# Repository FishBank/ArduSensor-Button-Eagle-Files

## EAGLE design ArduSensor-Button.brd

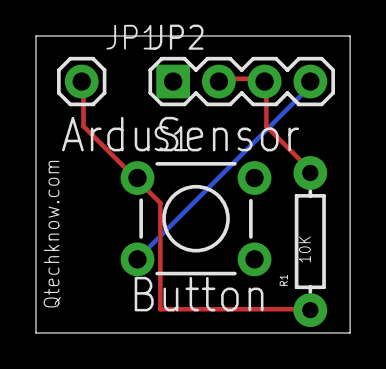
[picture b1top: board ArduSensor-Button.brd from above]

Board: 2 copper layers, 17.4 x 16.5 mm, 4 parts (0 on the bottom side), 3 nets.

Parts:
JP1: M01PTH; 1X01
JP2: 1X04
R1: AXIAL-0.3
S1: SWITCH-MOMENTARY-2PTH; TACTILE-PTH

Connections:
unnamed: JP1.1, R1.P$1, S1.1
unnamed: JP2.2, JP2.3, R1.P$2
unnamed: JP2.4, S1.3

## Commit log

2012-07-13 Schematic

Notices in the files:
parts and their libraries:
SFE Connectors: Licensing: CC v3.0 Share-Alike You are welcome to use this library for commercial purposes.
